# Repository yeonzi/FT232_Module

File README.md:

# FT232_module

USB转UART模块，使用FT232芯片

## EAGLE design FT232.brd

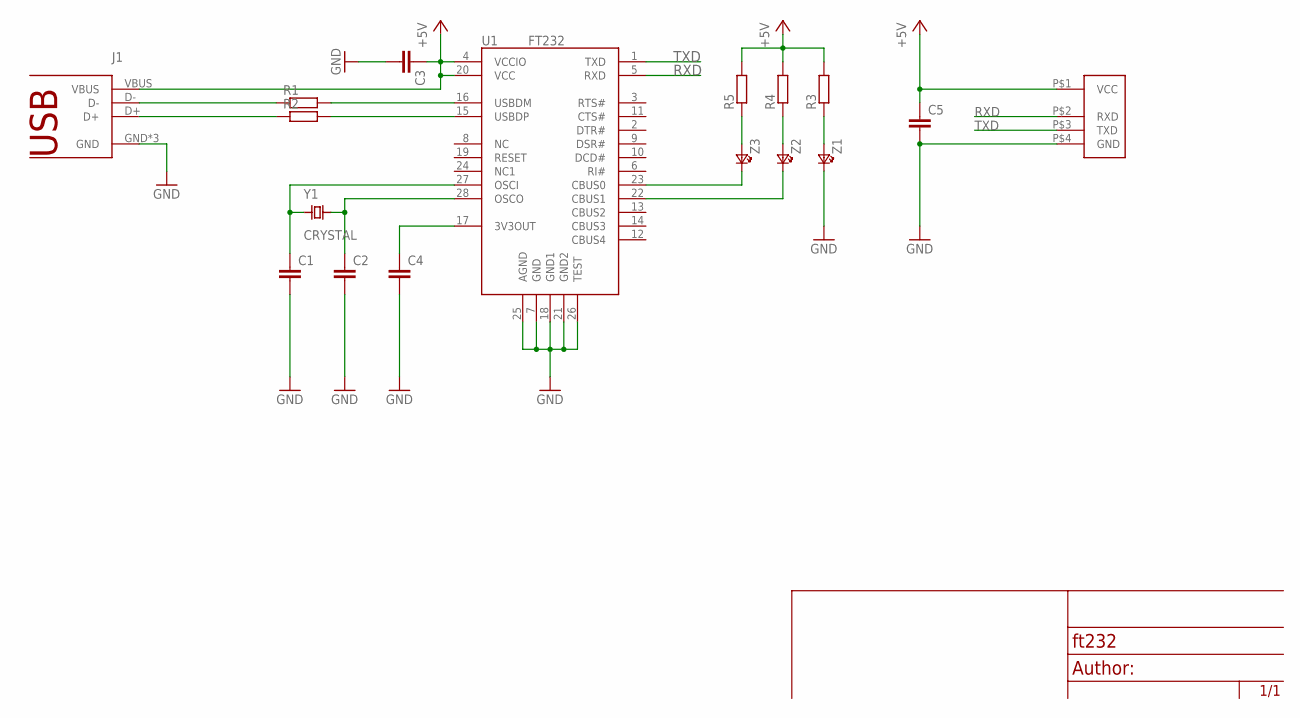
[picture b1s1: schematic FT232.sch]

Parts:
C1, C2, C3, C4, C5: CAPACITOR0402; C0402
J1: USBA; USB_A
J2: CON; CON4
R1, R2, R3, R4, R5: RESISTOR0402; R0402
U1: FT232; SSOP28
Y1: CRYSTAL; CRYSTAL5032
Z1, Z2, Z3: LED; LED0805

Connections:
+5V: C3.1, C5.1, J1.VBUS, J2.P$1 (VCC), R3.2, R4.2, R5.2, U1.4 (VCCIO), U1.20 (VCC)
D_N: R1.2, U1.16 (USBDM)
D_P: R2.2, U1.15 (USBDP)
GND: C1.2, C2.2, C3.2, C4.2, C5.2, J1.GND, J1.GND1 (GND), J1.GND2 (GND), J2.P$4 (GND), U1.7 (GND), U1.18 (GND1), U1.21 (GND2), U1.25 (AGND), U1.26 (TEST), Z1.K
unnamed: J1.D-, R1.1
unnamed: J1.D+, R2.1
unnamed: C2.1, U1.28 (OSCO), Y1.2
unnamed: C1.1, U1.27 (OSCI), Y1.1
unnamed: C4.1, U1.17 (3V3OUT)
unnamed: U1.23 (CBUS0), Z3.K
unnamed: U1.22 (CBUS1), Z2.K
unnamed: R5.1, Z3.A
unnamed: R4.1, Z2.A
unnamed: R3.1, Z1.A
RXD: J2.P$2 (RXD), U1.5 (RXD)
TXD: J2.P$3 (TXD), U1.1 (TXD)

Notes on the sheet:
Author:

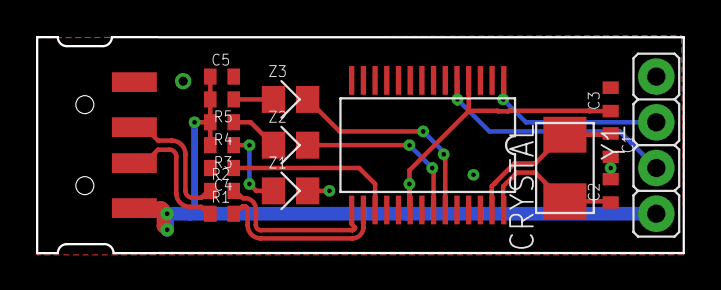
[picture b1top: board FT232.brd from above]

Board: 2 copper layers, 35.9 x 12.0 mm, 17 parts (0 on the bottom side), 16 nets.

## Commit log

2017-04-09 从别处粘贴来了一些元件符号
2017-04-09 从别处复制来了一个图纸frame
2017-04-10 FT232电路符号
2017-04-10 更新元件封装 似乎大概也许可能看起来我好像是把所有需要的元件封装与符号画完了
2017-04-10 我果然还是忘记了LED
2017-04-10 似乎应该大概可能也许我这次好像是真的把所有package搞定了
2017-04-10 我果然还是忘记了电源符号
2017-04-10 犯傻了，忘记有supply.lbr
2017-04-10 原理图完成
2017-04-10 PCB布局
2017-04-11 第一次布线尝试
2017-04-12 USB的另一种封装
2017-04-12 第二次布线尝试
2017-04-13 增加一个过孔
